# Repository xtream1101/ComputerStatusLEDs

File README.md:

ComputerStatusLEDs
==================

LEDs that will display different colors giving you a quick look of a status

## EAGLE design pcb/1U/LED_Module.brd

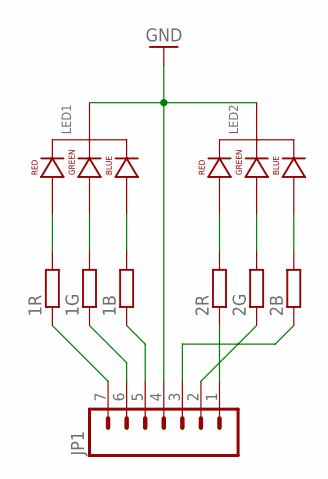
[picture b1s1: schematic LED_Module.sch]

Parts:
1B, 1G, 1R, 2B, 2G, 2R: RR0603; R0603
JP1: M07; 1X07
LED1, LED2: LED-RGB-CC-THRUDIFFUSE; LED-RGB-THRU

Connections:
GND: JP1.4, LED1.2 (CATHODE), LED2.2 (CATHODE)
unnamed: 2R.2, LED2.1 (RED_CATHODE)
unnamed: 2G.2, LED2.3 (GREEN_CATHODE)
unnamed: 2B.2, LED2.4 (BLUE_CATHODE)
unnamed: 1R.2, LED1.1 (RED_CATHODE)
unnamed: 1G.2, LED1.3 (GREEN_CATHODE)
unnamed: 1B.2, LED1.4 (BLUE_CATHODE)
unnamed: 1R.1, JP1.7
unnamed: 1G.1, JP1.6
unnamed: 1B.1, JP1.5
unnamed: 2R.1, JP1.1
unnamed: 2G.1, JP1.2
unnamed: 2B.1, JP1.3

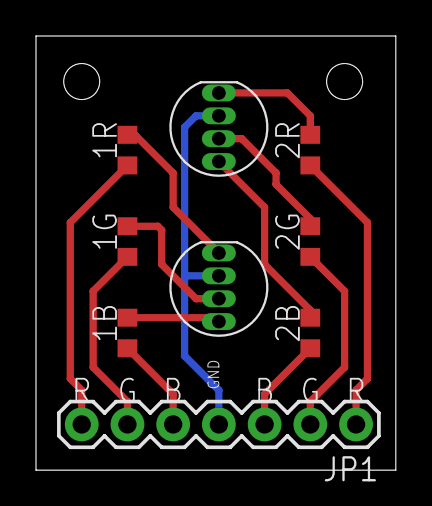
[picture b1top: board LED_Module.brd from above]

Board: 2 copper layers, 20.0 x 24.1 mm, 9 parts (0 on the bottom side), 13 nets.

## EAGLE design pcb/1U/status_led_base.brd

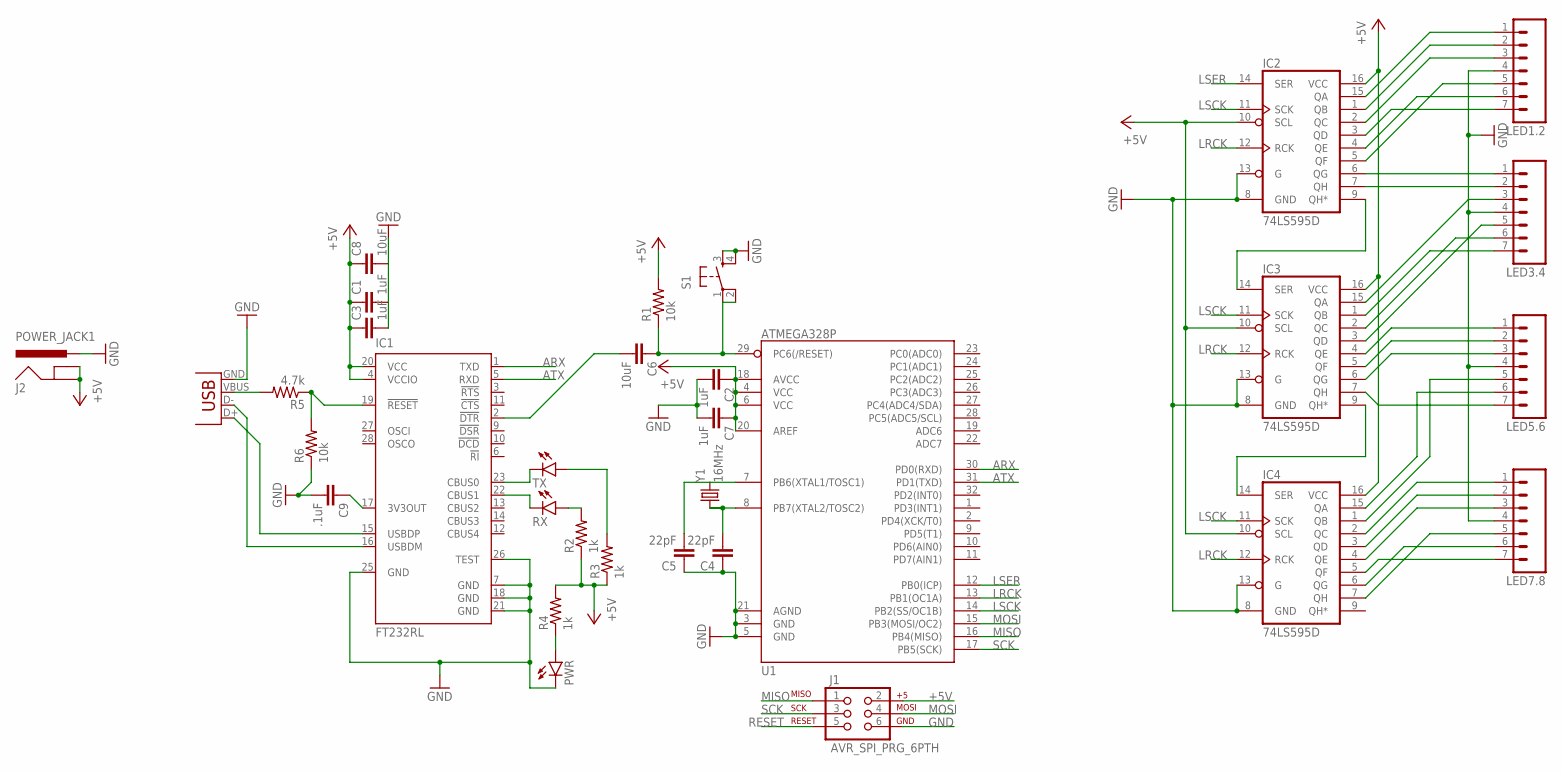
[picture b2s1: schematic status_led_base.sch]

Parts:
C1, C2, C3, C7: 1uF; 0603-CAP
C4, C5: 22pF; 0603-CAP
C6, C8: 10uF; 0603-CAP
C9: .1uF; 0603-CAP
IC1: FT232RL; SSOP28
IC2, IC3, IC4: 74LS595D; SO16
J1: AVR_SPI_PRG_6PTH; 2X3
J2: POWER_JACK1; POWER_JACK_SMD_OVERPASTE_REDBOARD_0603
JP1: USBSMD; USB-MINIB
LED1.2, LED3.4, LED5.6, LED7.8: M07; 1X07
PWR: LED0603; LED-0603
R1, R6: 10k; 0603-RES
R2, R3, R4: 1k; 0603-RES
R5: 4.7k; 0603-RES
RX: LED0603; LED-0603
S1: TAC_SWITCHSMD; TACTILE-SWITCH-SMD
TX: LED0603; LED-0603
U1: ATMEGA328P; TQFP32-08
Y1: 16MHz; HC49UP

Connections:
+5V: C1.1, C2.1, C3.1, C7.1, C8.1, IC1.4 (VCCIO), IC1.20 (VCC), IC2.10 (SCL), IC2.16 (VCC), IC3.10 (SCL), IC3.16 (VCC), IC4.10 (SCL), IC4.16 (VCC), J1.2, J2.GND (GNDBREAK), J2.P$4 (GND), R1.2, R2.1, R3.1, R4.2, U1.4 (VCC), U1.6 (VCC), U1.18 (AVCC), U1.20 (AREF)
ARX: IC1.1 (TXD), U1.30 (PD0(RXD))
ATX: IC1.5 (RXD), U1.31 (PD1(TXD))
GND: C1.2, C2.2, C3.2, C4.1, C5.1, C7.2, C8.2, C9.2, IC1.7 (GND), IC1.18 (GND), IC1.21 (GND), IC1.25 (GND), IC1.26 (TEST), IC2.8 (GND), IC2.13 (G), IC3.8 (GND), IC3.13 (G), IC4.8 (GND), IC4.13 (G), J1.6, J2.VIN0 (PWR), JP1.GND, LED1.2.4, LED3.4.4, LED5.6.4, LED7.8.4, PWR.C, R6.1, S1.3, S1.4, U1.3 (GND), U1.5 (GND), U1.21 (AGND)
LRCK: IC2.12 (RCK), IC3.12 (RCK), IC4.12 (RCK), U1.13 (PB1(OC1A))
LSCK: IC2.11 (SCK), IC3.11 (SCK), IC4.11 (SCK), U1.14 (PB2(SS/OC1B))
LSER: IC2.14 (SER), U1.12 (PB0(ICP))
MISO: J1.1, U1.16 (PB4(MISO))
MOSI: J1.4, U1.15 (PB3(MOSI/OC2))
unnamed: IC1.16 (USBDM), JP1.D-
unnamed: IC1.15 (USBDP), JP1.D+
unnamed: IC4.15 (QA), LED5.6.6
unnamed: R3.2, TX.A
unnamed: R2.2, RX.A
unnamed: C6.2, IC1.2 (!DTR)
unnamed: PWR.A, R4.1
unnamed: IC2.15 (QA), LED1.2.1
unnamed: IC1.23 (CBUS0), TX.C
unnamed: IC1.22 (CBUS1), RX.C
unnamed: C9.1, IC1.17 (3V3OUT)
unnamed: JP1.VBUS, R5.2
unnamed: C5.2, U1.7 (PB6(XTAL1/TOSC1)), Y1.2
unnamed: C4.2, U1.8 (PB7(XTAL2/TOSC2)), Y1.1
unnamed: IC2.1 (QB), LED1.2.2
unnamed: IC2.2 (QC), LED1.2.3
unnamed: IC2.3 (QD), LED1.2.7
unnamed: IC2.4 (QE), LED1.2.6
unnamed: IC2.5 (QF), LED1.2.5
unnamed: IC2.9 (QH*), IC3.14 (SER)
unnamed: IC3.9 (QH*), IC4.14 (SER)
unnamed: IC2.6 (QG), LED3.4.1
unnamed: IC2.7 (QH), LED3.4.2
unnamed: IC3.15 (QA), LED3.4.3
unnamed: IC3.1 (QB), LED3.4.7
unnamed: IC3.2 (QC), LED3.4.6
unnamed: IC3.3 (QD), LED3.4.5
unnamed: IC3.4 (QE), LED5.6.1
unnamed: IC3.5 (QF), LED5.6.2
unnamed: IC3.6 (QG), LED5.6.3
unnamed: IC3.7 (QH), LED5.6.7
unnamed: IC4.1 (QB), LED5.6.5
unnamed: IC4.2 (QC), LED7.8.1
unnamed: IC4.3 (QD), LED7.8.2
unnamed: IC4.4 (QE), LED7.8.3
unnamed: IC4.5 (QF), LED7.8.7
unnamed: IC4.6 (QG), LED7.8.6
unnamed: IC4.7 (QH), LED7.8.5
unnamed: IC1.19 (!RESET), R5.1, R6.2
RESET: C6.1, J1.5, R1.1, S1.1, S1.2, U1.29 (PC6(/RESET))
SCK: J1.3, U1.17 (PB5(SCK))

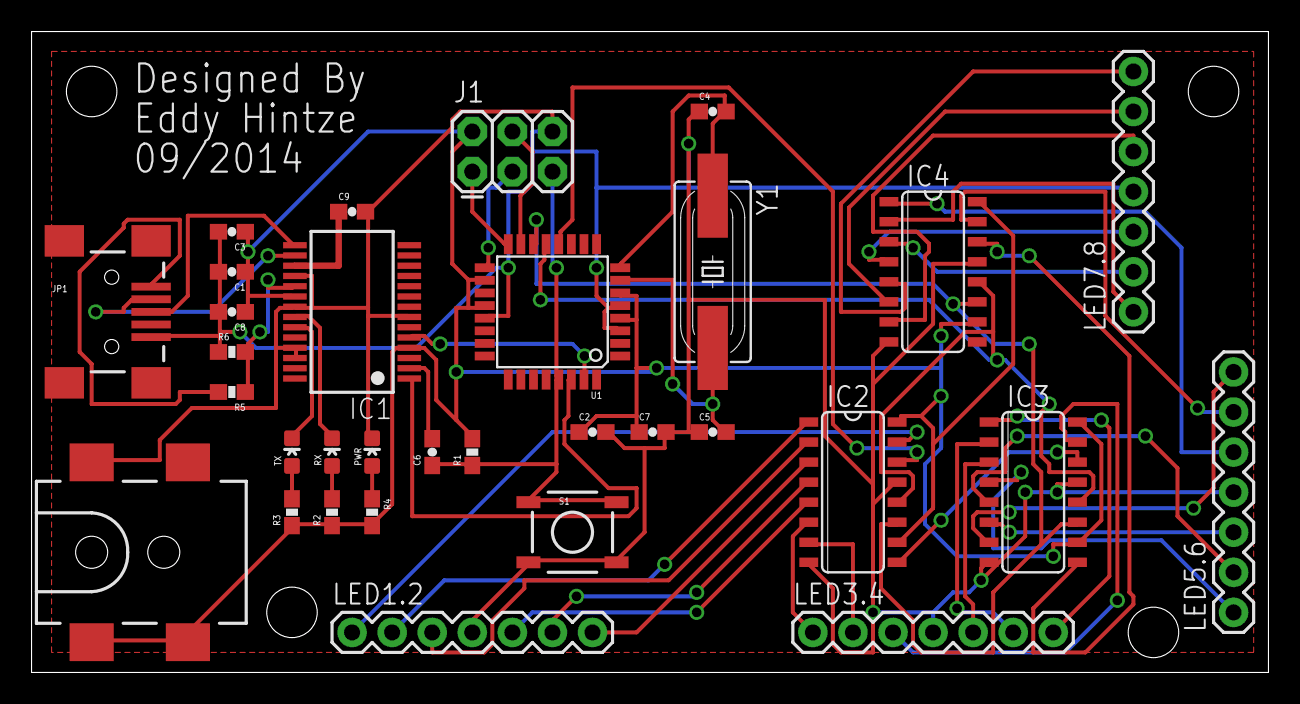
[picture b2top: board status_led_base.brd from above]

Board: 2 copper layers, 78.4 x 40.6 mm, 32 parts (0 on the bottom side), 50 nets.

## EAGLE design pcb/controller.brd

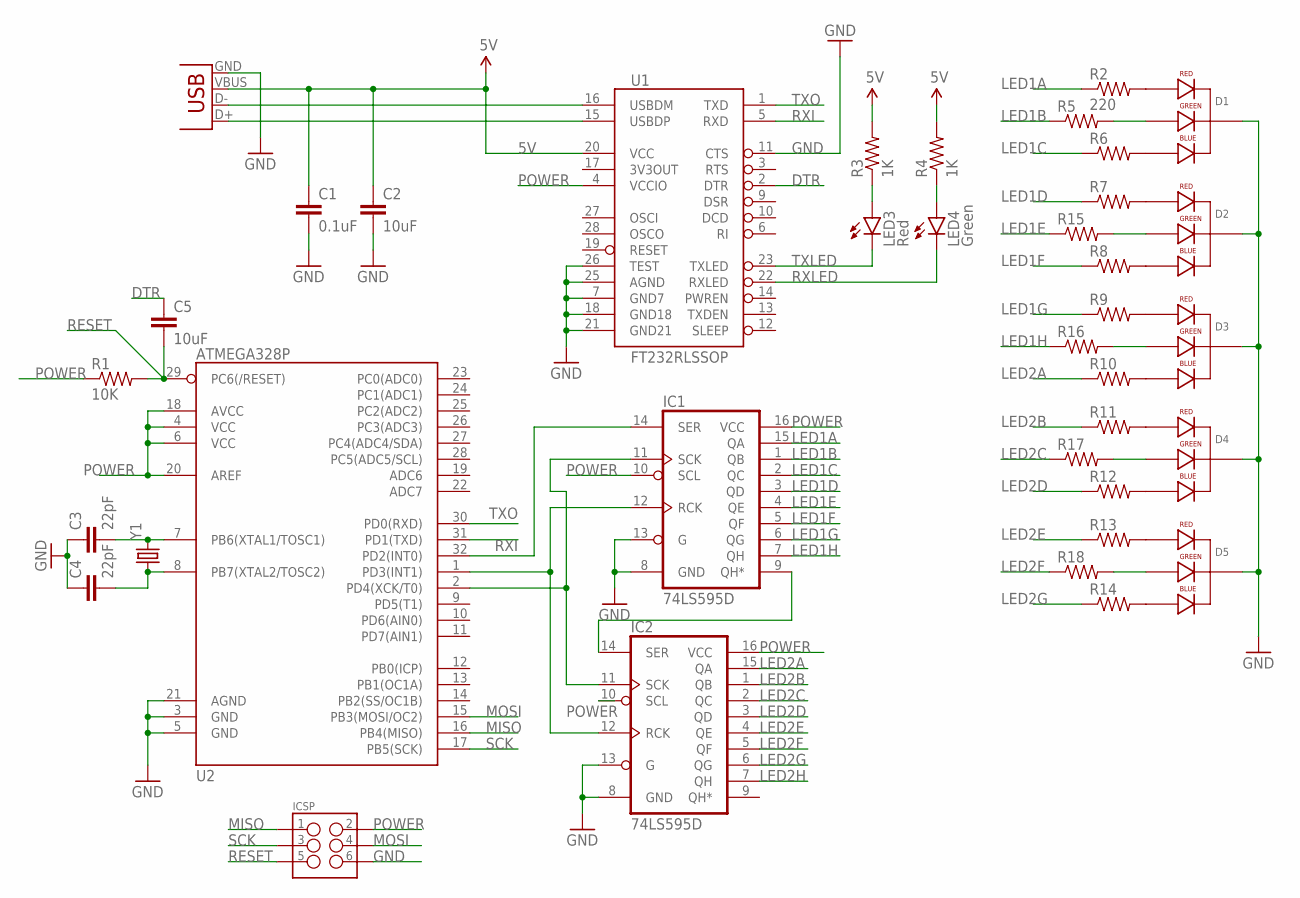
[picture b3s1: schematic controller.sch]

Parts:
C1: 0.1uF; 0805
C2, C5: 10uF; 0805
C3, C4: 22pF; 0805
D1, D2, D3, D4, D5: LED-RGB-CC-THRUDIFFUSE; LED-RGB-THRU
IC1, IC2: 74LS595D; SO16
ICSP: M03X2POGO_PINS; 2X3_POGO
LED3: Red; LED-1206
LED4: Green; LED-1206
R1: 10K; 0805
R2: 220; 0805
R3, R4: 1K; 0805
R5, R6, R7, R8, R9, R10, R11, R12, R13, R14, R15, R16, R17, R18: RESISTOR0805-RES; 0805
U1: FT232RLSSOP; SSOP28DB
U2: ATMEGA328P; TQFP32-08
X2: USB-SMD-NS; USB-MINIB-NOSTOP
Y1: CRYSTALHC49US; HC49US

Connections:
5V: C1.1, C2.1, R3.2, R4.2, U1.20 (VCC), X2.VBUS
DTR: C5.1, U1.2 (DTR)
GND: C1.2, C2.2, C3.1, C4.1, D1.2 (CATHODE), D2.2 (CATHODE), D3.2 (CATHODE), D4.2 (CATHODE), D5.2 (CATHODE), IC1.8 (GND), IC1.13 (G), IC2.8 (GND), IC2.13 (G), ICSP.P$6 (6), U1.7 (GND7), U1.11 (CTS), U1.18 (GND18), U1.21 (GND21), U1.25 (AGND), U1.26 (TEST), U2.3 (GND), U2.5 (GND), U2.21 (AGND), X2.GND
LED1A: IC1.15 (QA), R2.1
LED1B: IC1.1 (QB), R5.1
LED1C: IC1.2 (QC), R6.1
LED1D: IC1.3 (QD), R7.1
LED1E: IC1.4 (QE), R15.1
LED1F: IC1.5 (QF), R8.1
LED1G: IC1.6 (QG), R9.1
LED1H: IC1.7 (QH), R16.1
LED2A: IC2.15 (QA), R10.1
LED2B: IC2.1 (QB), R11.1
LED2C: IC2.2 (QC), R17.1
LED2D: IC2.3 (QD), R12.1
LED2E: IC2.4 (QE), R13.1
LED2F: IC2.5 (QF), R18.1
LED2G: IC2.6 (QG), R14.1
LED2H: IC2.7 (QH)
MISO: ICSP.P$1 (1), U2.16 (PB4(MISO))
MOSI: ICSP.P$4 (4), U2.15 (PB3(MOSI/OC2))
unnamed: LED3.A, R3.1
unnamed: LED4.A, R4.1
unnamed: IC1.9 (QH*), IC2.14 (SER)
unnamed: IC1.14 (SER), U2.32 (PD2(INT0))
unnamed: IC1.12 (RCK), IC2.12 (RCK), U2.1 (PD3(INT1))
unnamed: IC1.11 (SCK), IC2.11 (SCK), U2.2 (PD4(XCK/T0))
unnamed: C3.2, U2.7 (PB6(XTAL1/TOSC1)), Y1.2
unnamed: C4.2, U2.8 (PB7(XTAL2/TOSC2)), Y1.1
unnamed: D1.1 (RED_CATHODE), R2.2
unnamed: D1.4 (BLUE_CATHODE), R6.2
unnamed: D2.1 (RED_CATHODE), R7.2
unnamed: D2.4 (BLUE_CATHODE), R8.2
unnamed: D3.1 (RED_CATHODE), R9.2
unnamed: D3.4 (BLUE_CATHODE), R10.2
unnamed: D4.1 (RED_CATHODE), R11.2
unnamed: D4.4 (BLUE_CATHODE), R12.2
unnamed: D5.1 (RED_CATHODE), R13.2
unnamed: D5.4 (BLUE_CATHODE), R14.2
unnamed: D1.3 (GREEN_CATHODE), R5.2
unnamed: D2.3 (GREEN_CATHODE), R15.2
unnamed: D3.3 (GREEN_CATHODE), R16.2
unnamed: D4.3 (GREEN_CATHODE), R17.2
unnamed: D5.3 (GREEN_CATHODE), R18.2
POWER: IC1.10 (SCL), IC1.16 (VCC), IC2.10 (SCL), IC2.16 (VCC), ICSP.P$2 (2), R1.1, U1.4 (VCCIO), U2.4 (VCC), U2.6 (VCC), U2.18 (AVCC), U2.20 (AREF)
RESET: C5.2, ICSP.P$5 (5), R1.2, U2.29 (PC6(/RESET))
RXI: U1.5 (RXD), U2.31 (PD1(TXD))
RXLED: LED4.C, U1.22 (RXLED)
SCK: ICSP.P$3 (3), U2.17 (PB5(SCK))
TXLED: LED3.C, U1.23 (TXLED)
TXO: U1.1 (TXD), U2.30 (PD0(RXD))
USB_D+: U1.15 (USBDP), X2.D+
USB_D-: U1.16 (USBDM), X2.D-

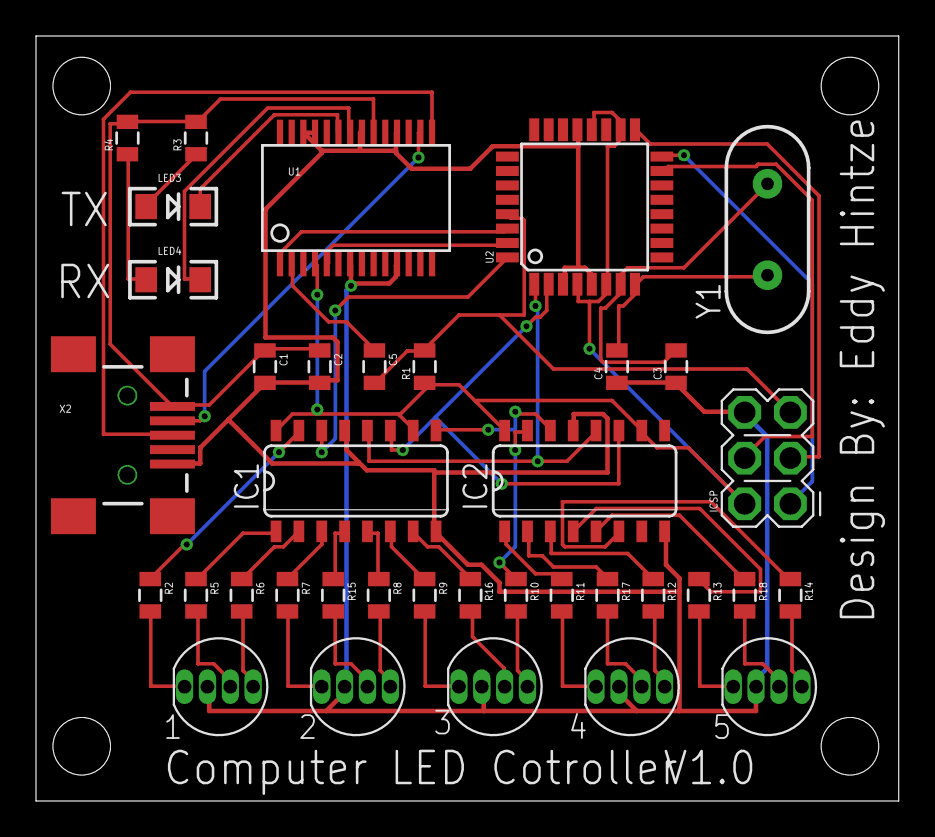
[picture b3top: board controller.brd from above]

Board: 2 copper layers, 47.9 x 42.5 mm, 37 parts (0 on the bottom side), 52 nets.

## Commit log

2014-06-28 Initial code upload
2014-06-28 Created loop for cmd check
2014-06-30 Added test scripts
2014-06-30 Added model number feedback
2014-06-30 Aded .gitignore
2014-06-30 Created layout for client program
2014-06-30 Created action for checkbox
2014-06-30 LED now changes via checkbox command
2014-06-30 Added threading for scripts
2014-06-30 Added json support to save/load data
2014-07-01 Started pcb design
2014-07-01 Connected FTDI and atmega328
2014-07-01 Added ISCP to atmega328
2014-07-01 Connected 2 74hc595 to the atmega328
2014-07-01 Connected 5 RGB LED's
2014-07-01 Re-connected RGB LEDs in a cleaner way
2014-07-01 Basic board layout
2014-07-01 Rearranged board layout
2014-07-01 Just before auto route
2014-07-02 PCB board auto routed
2014-10-06 Updated pcb layouts
2014-10-06 Checkbox status is now saved
    Scripts will auto start if checked
2014-10-06 When checked, edit fields are disabled
2014-10-06 Created logs
    Every time a script runs, it is logged with a timestamp
2014-10-06 When thread is killed LED turns off
2014-10-06 Support for multiple shift registers

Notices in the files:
parts and their libraries:
SparkFun-LED: Licensing: Creative Commons ShareAlike 4.0 International - https://creativecommons.org/licenses/by-sa/4.0
